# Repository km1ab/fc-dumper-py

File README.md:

# FC dumper py

- Dumper for fc by Python.
- This dumper is a HAT for Raspberry Pi and we also publish the source code to make it work in this repository.

## Environment
- Raspberry pi 3 b+, or later
- Raspberry pi zero, or later

```
Unsupported on Raspberry pi 5. "RPi.GPIO" is no longer available from Raspberry pi 5. 
We are currently looking into alternatives.
```

## How to use
At Raspberry pi, or remote connecting (ex ssh,...)
```
pip install RPi.GPIO
python3 fc_dumper.py -o filename
```

```
$ python3 fc_dumpter.py --help
usage: fc_dumpter.py [-h] [-o OUTPUT_FILE] [-p {8K,16K,32K}] [-c {1K,8K,16K,32K}] [-a {mapper0,mapper1,mapper3,mapper66,mapper23}] [-m {dumper,led_test}] [-d [DEBUG]] [-i [INFO]] [-s SIZE]
                     [-D [LED_DUTY ...]] [-F [LED_FREQ ...]] [-N [LED_NUMBER ...]] [-T LED_TIME]

options:
  -h, --help            show this help message and exit
  -o OUTPUT_FILE, --output_file OUTPUT_FILE
                        output file name; (default: output.nes)
  -p {8K,16K,32K}, --prg_rom_size {8K,16K,32K}
                        program rom size select; (default: 16K)
  -c {1K,8K,16K,32K}, --chr_rom_size {1K,8K,16K,32K}
                        charactor rom size select; (default: 8K)
  -a {mapper0,mapper1,mapper3,mapper66,mapper23}, --mapper {mapper0,mapper1,mapper3,mapper66,mapper23}
                        mapper select; In mapper 23, specify the size of the bank in options '-p' and '-c'. (default: mapper0)
  -m {dumper,led_test}, --mode {dumper,led_test}
                        mode (default: dumper)
  -d [DEBUG], --debug [DEBUG]
                        debug log (default: False)
  -i [INFO], --info [INFO]
                        game infomation (default: False)
  -s SIZE, --size SIZE  read size (default: 256)
  -D [LED_DUTY ...], --led_duty [LED_DUTY ...]
                        LED testing only (default: [1])
  -F [LED_FREQ ...], --led_freq [LED_FREQ ...]
                        LED testing only (default: [20])
  -N [LED_NUMBER ...], --led_number [LED_NUMBER ...]
                        LED testing only (default: [0])
  -T LED_TIME, --led_time LED_TIME
                        LED testing only (default: 5)
```

## Hardware
- PCB-top

- PCB-bottom

## Parts list
必須

| 名称                             | 数量 | 入手先      | 備考                                                                      |
|--------------------------------|----|----------|-------------------------------------------------------------------------|
| PCB-top (rev1.0)               | 1  | 頒布予定     | 本ページのHardwareを参照                                                        |
| PCB-bottom (rev1.0)            | 1  | 頒布予定     | 本ページのHardwareを参照                                                        |
| ラズパイ 3 b+                      | 1  | メルカリ？など  | ラズパイ5が発売されました。少々高いですが、容量の少ない方が比較的入手しやすいようです。2024/03現在。                    |
| CR22A-60D-2.54DS(70)           | 1  | ⇒⇒⇒      | googleにて、CR22A-60D-2.54DS(70)で検索すると、ある程度ヒットします。                         |
| 抵抗内蔵５ｍｍＬＥＤ（※）                  | 1  | 秋月電子     | https://akizukidenshi.com/catalog/g/gI-12517/                           |
| 小型スライドスイッチ　１回路２接点              | 1  | 秋月電子     | https://akizukidenshi.com/catalog/g/gP-12723/                           |
| 8ビット双方向ロジックレベル変換モジュール（FXMA108） | 1  | 秋月電子     | https://akizukidenshi.com/catalog/g/g104522/                            |
| 74HC244                        | 1  | マルツオンライン | https://www.marutsu.co.jp/GoodsDetail.jsp?salesGoodsCode=37576&shopNo=3 |
| 74HC4040                       | 2  | マルツオンライン | https://www.marutsu.co.jp/pc/i/18963/                                   |
| Raspberry Pi専用スペーサー（MPS-M2611） | 1  | サンハヤト    | https://shop.sunhayato.co.jp/products/mps-m2611                         |
| 六角オネジ・メネジ　ＭＢ２６－１１              | 4  | 秋月電子     | https://akizukidenshi.com/catalog/g/gP-11546/                           |
| ピンソケット (メス) 2×20 (40P)         | 1  | 秋月電子     | https://akizukidenshi.com/catalog/g/g100085/                            |
| ピンソケット(メス) 1×12(12P)           | 1  | 秋月電子     | https://akizukidenshi.com/catalog/g/g110101/                            |
| ピンソケット(メス) 1×10(10P)           | 1  | 秋月電子     | https://akizukidenshi.com/catalog/g/g103786/                            |
| ピンヘッダ 1×4 (4P)　10個入り（※）        | 1  | 秋月電子     | https://akizukidenshi.com/catalog/g/g103950/                            |
| ピンヘッダ 1×40 (40P)               | 1  | 秋月電子     | https://akizukidenshi.com/catalog/g/g100167/                            |
| ICソケット (16P)　10個入り（※）          | 1  | 秋月電子     | https://akizukidenshi.com/catalog/g/g100007/                            |
| ICソケット (20P)　10個入り（※）          | 1  | 秋月電子     | https://akizukidenshi.com/catalog/g/g100009/                            |

※LEDは、いかにも電源ONでスライドスイッチ真横のLED(D2)が光りそうですが、実際D3の方が光ります。<br>
　また、必ずしも内臓抵抗のものである必要がありません。<br>
　5mm LEDと抵抗の組み合わせでも良いです。<br>
　回路図をご覧頂くとわかるかと思います。<br>
※ピンヘッダ 1×4 (4P)は、1個しか使いません。バラで購入できるならそれで問題ありません。<br>
※ICソケットはそれぞれ2個使います。バラで購入できるならそれで問題ありません。<br>
　ただ、ICソケットは有りでも無しでも好きな方で。<br>

#### オプション
- 抵抗内蔵５ｍｍＬＥＤ x2
- トランジスタ　２ＳＣ１８１５ x2
- ※抵抗内蔵LEDを使わない場合は、抵抗x3（抵抗値はLEDのスペックによる）
- Bottom ケース：3Dプリンタで作りました。3B+用に適当に作っています　(データ：stl/raspi_case_4_2.stl)
- ピンヘッダ 2×20 (40P) ※2x4(8P)分しか使いません。デバッグ用なので無くても問題ありせん。
### 完成図
- ラズパイと接続するとこのような見た目になります。
- ２段のスタック構造になっています。
- ※Raspberry Pi専用スペーサーのナットは使いませんでした。

### 分割した様子
#### face and bottom
- face

- bottom

### 留意事項
#### FXMA108の取り付けについて
- FXMA108のキットは、付属のピンヘッダをそのまま取り付けると、隣のHC244より背が高くなります。<br>それに伴い、PCB-TOPをスタックする時に干渉してしまいますので、以下に取付方法を記載致します。
- 方法１
  - ピンヘッダの足を適当な長さに切りそろえて下さい。
  - また、付属のピンヘッダの足は太いので、ICソケットに若干強引に差し込みます（問題なくささりますが）。
  - なので、気になる方は細ピンヘッダを使うと良いかもしれません。
- もう１つの方法
  - ICソケットも、ピンヘッダも使わずに直に取り付けてしまう方法です。
  - FXMA108のキットに以下のような説明がありました。簡単な方をお試しください。
```
スルーホール部分をルータ加工することで、ユニバーサル基板等に直接ハンダ付け可能となっています。（※）
```
※8ビット双方向ロジックレベル変換モジュールのマニュアルより引用。

### PCB design

#### top PCB

#### bottom PCB

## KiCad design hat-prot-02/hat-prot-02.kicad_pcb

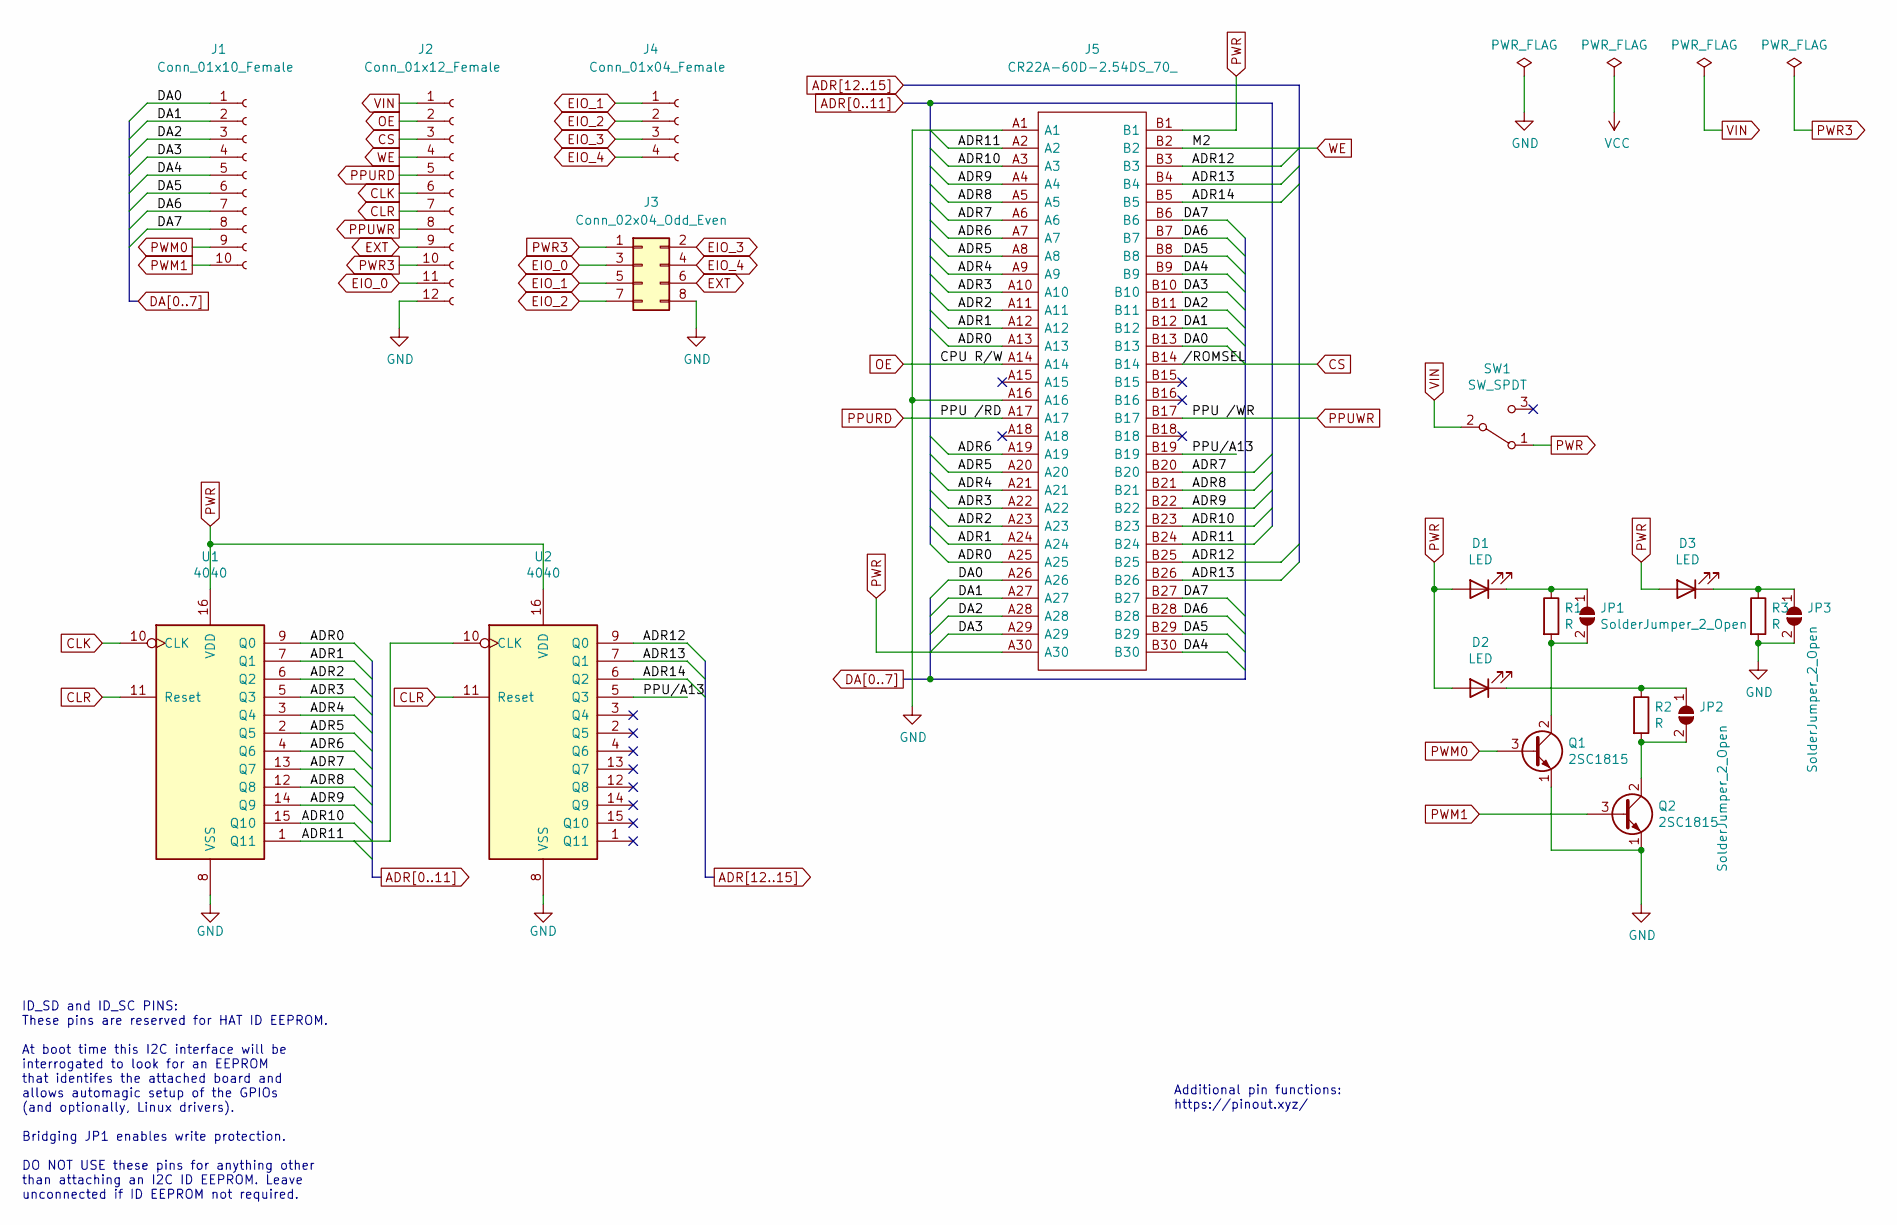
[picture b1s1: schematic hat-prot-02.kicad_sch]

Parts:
D1, D2, D3: LED; LED_D3.0mm
J1: Conn_01x10_Female; PinSocket_1x10_P2.54mm_Vertical
J2: Conn_01x12_Female; PinSocket_1x12_P2.54mm_Vertical
J3: Conn_02x04_Odd_Even; PinHeader_2x04_P2.54mm_Vertical
J4: Conn_01x04_Female; PinSocket_1x04_P2.54mm_Vertical
J5: CR22A-60D-2.54DS_70_; CR22A60D254DS70; Manufacturer_Part_Number CR22A-60D-2.54DS(70)
JP1, JP2, JP3: SolderJumper_2_Open; SolderJumper-2_P1.3mm_Open_RoundedPad1.0x1.5mm
Q1, Q2: 2SC1815; TO-92_Inline
R1, R2, R3: R; R_Axial_DIN0204_L3.6mm_D1.6mm_P5.08mm_Horizontal
SW1: SW_SPDT; PinHeader_1x03_P2.54mm_Vertical
U1, U2: 4040; DIP-16_W7.62mm

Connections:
/PPU/A13: J5.B19, U2.5 (Q3)
ADR0: J5.A13, J5.A25, U1.9 (Q0)
ADR1: J5.A12, J5.A24, U1.7 (Q1)
ADR2: J5.A11, J5.A23, U1.6 (Q2)
ADR3: J5.A10, J5.A22, U1.5 (Q3)
ADR4: J5.A9, J5.A21, U1.3 (Q4)
ADR5: J5.A8, J5.A20, U1.2 (Q5)
ADR6: J5.A7, J5.A19, U1.4 (Q6)
ADR7: J5.A6, J5.B20, U1.13 (Q7)
ADR8: J5.A5, J5.B21, U1.12 (Q8)
ADR9: J5.A4, J5.B22, U1.14 (Q9)
ADR10: J5.A3, J5.B23, U1.15 (Q10)
ADR11: J5.A2, J5.B24, U1.1 (Q11), U2.10 (CLK)
ADR12: J5.B3, J5.B25, U2.9 (Q0)
ADR13: J5.B4, J5.B26, U2.7 (Q1)
ADR14: J5.B5, U2.6 (Q2)
CLK: J2.6, U1.10 (CLK)
CLR: J2.7, U1.11 (Reset), U2.11 (Reset)
CS: J2.3, J5.B14
DA0: J1.1, J5.A26, J5.B13
DA1: J1.2, J5.A27, J5.B12
DA2: J1.3, J5.A28, J5.B11
DA3: J1.4, J5.A29, J5.B10
DA4: J1.5, J5.B9, J5.B30
DA5: J1.6, J5.B8, J5.B29
DA6: J1.7, J5.B7, J5.B28
DA7: J1.8, J5.B6, J5.B27
EIO_0: J2.11, J3.3
EIO_1: J3.5, J4.1
EIO_2: J3.7, J4.2
EIO_3: J3.2, J4.3
EIO_4: J3.4, J4.4
EXT: J2.9, J3.6
unnamed: D1.1 (K), JP1.1 (A), R1.1
unnamed: D2.1 (K), JP2.1 (A), R2.1
unnamed: D3.1 (K), JP3.1 (A), R3.1
unnamed: JP1.2 (B), Q1.2 (C), R1.2
unnamed: JP2.2 (B), Q2.2 (C), R2.2
OE: J2.2, J5.A14
PPURD: J2.5, J5.A17
PPUWR: J2.8, J5.B17
PWM0: J1.9, Q1.3 (B)
PWM1: J1.10, Q2.3 (B)
PWR: D1.2 (A), D2.2 (A), D3.2 (A), J5.A30, J5.B1, SW1.1 (A), U1.16 (VDD), U2.16 (VDD)
WE: J2.4, J5.B2

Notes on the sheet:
Additional pin functions: https://pinout.xyz/
ID_SD and ID_SC PINS: These pins are reserved for HAT ID EEPROM. At boot time this I2C interface will be interrogated to look for an EEPROM that identifes the attached board and allows automagic setup of the GPIOs (and optionally, Linux drivers). Bridging JP1 enables write protection. DO NOT USE th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

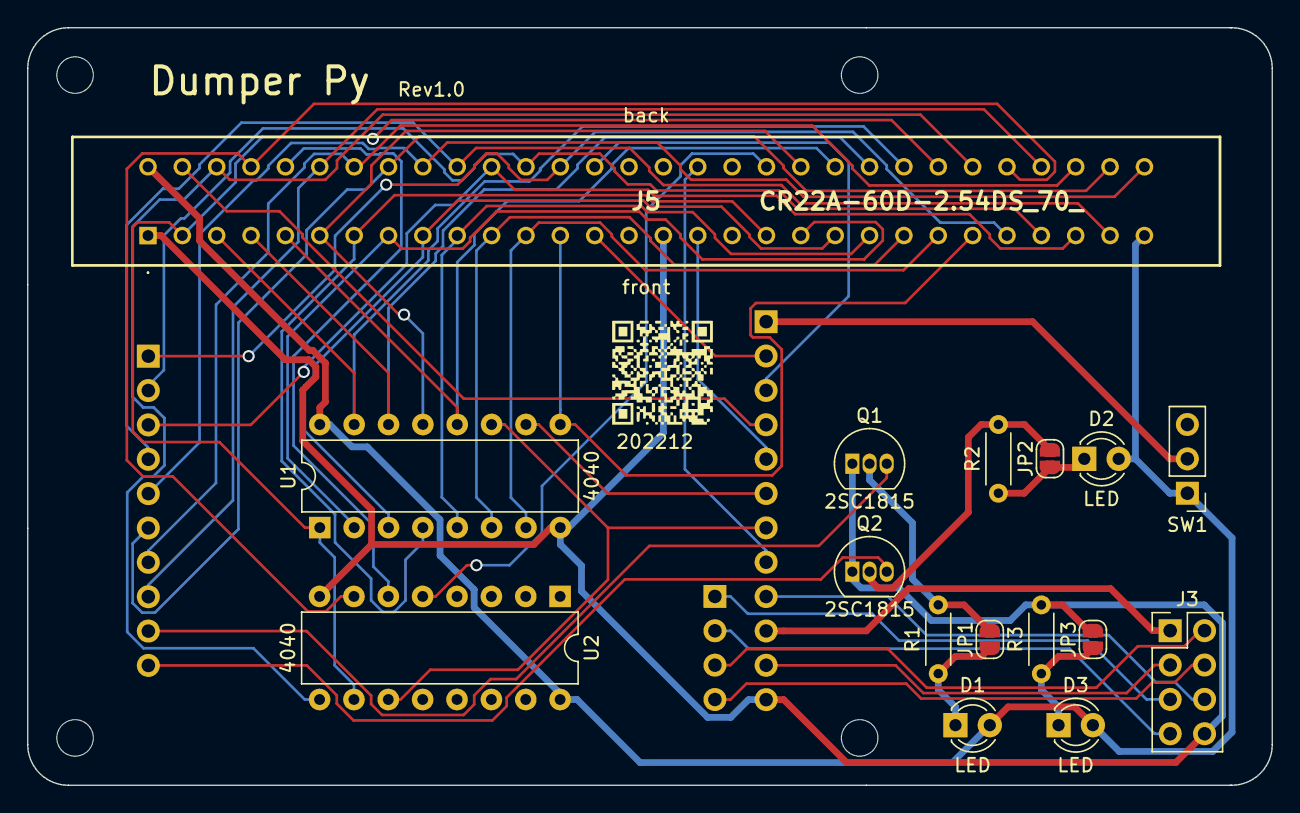
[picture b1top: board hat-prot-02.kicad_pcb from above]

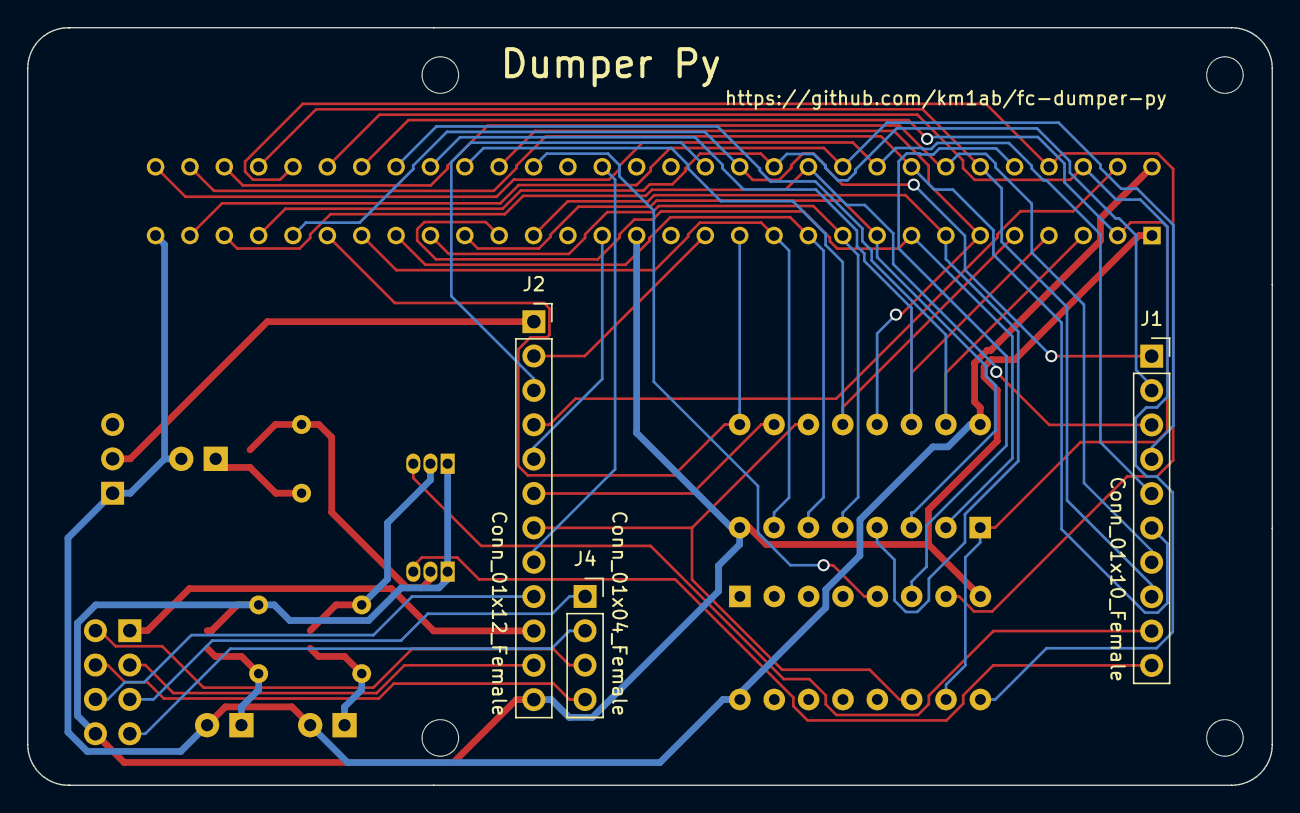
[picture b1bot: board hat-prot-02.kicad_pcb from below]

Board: 2 copper layers, 92.0 x 56.0 mm, 23 parts (3 on the bottom side), 48 nets.

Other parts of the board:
MH1, MH2, MH3, MH4: MountingHole_2.7mm_M2.5

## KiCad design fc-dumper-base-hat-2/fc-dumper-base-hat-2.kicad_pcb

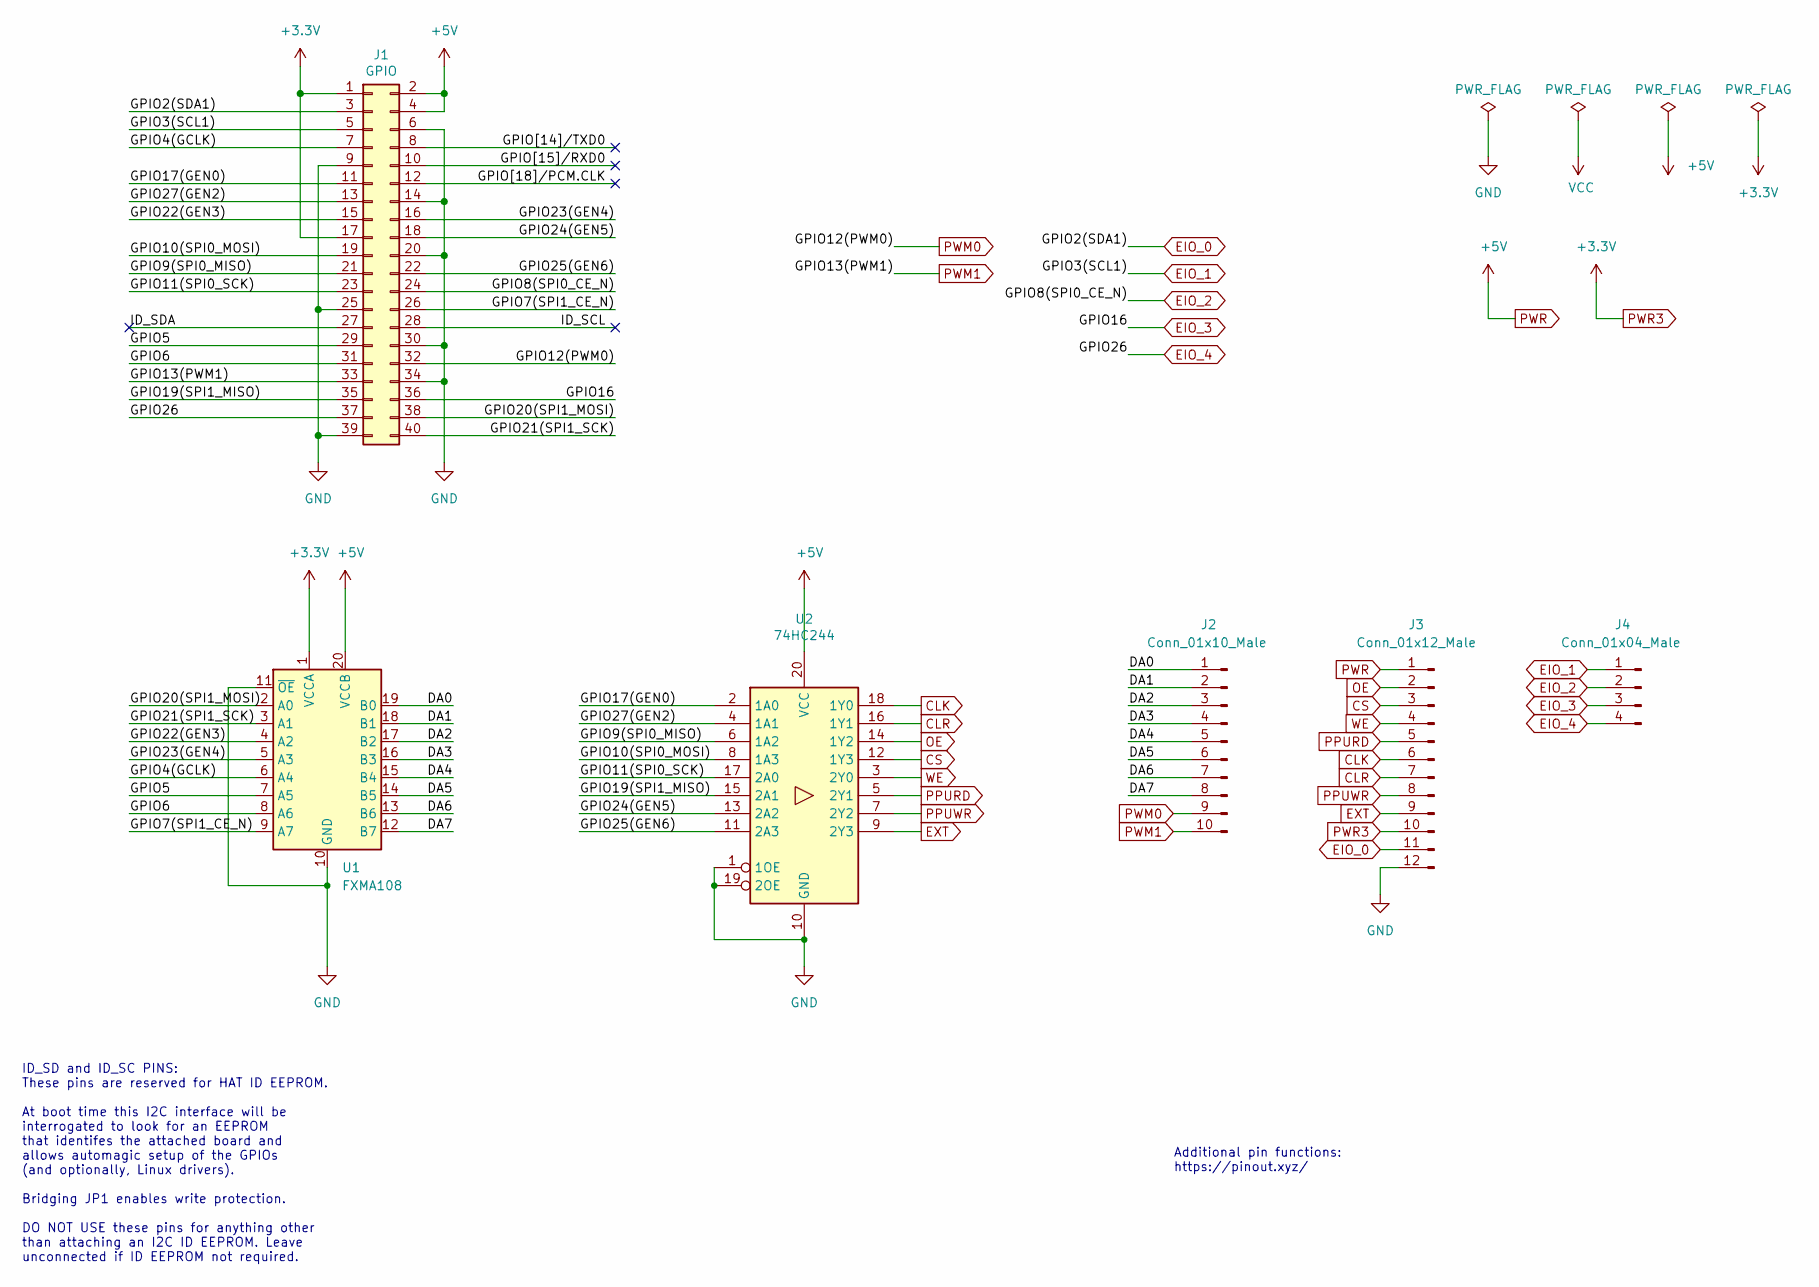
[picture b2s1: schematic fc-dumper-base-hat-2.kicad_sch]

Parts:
J1: GPIO; PinSocket_2x20_P2.54mm_Vertical
J2: Conn_01x10_Male; PinHeader_1x10_P2.54mm_Vertical
J3: Conn_01x12_Male; PinHeader_1x12_P2.54mm_Vertical
J4: Conn_01x04_Male; PinHeader_1x04_P2.54mm_Vertical
U1: FXMA108; DIP-20_W7.62mm
U2: 74HC244; DIP-20_W7.62mm

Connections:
/DA0: J2.1, U1.19 (B0)
/DA1: J2.2, U1.18 (B1)
/DA2: J2.3, U1.17 (B2)
/DA3: J2.4, U1.16 (B3)
/DA4: J2.5, U1.15 (B4)
/DA5: J2.6, U1.14 (B5)
/DA6: J2.7, U1.13 (B6)
/DA7: J2.8, U1.12 (B7)
/GPIO4(GCLK): J1.7, U1.6 (A4)
/GPIO5: J1.29, U1.7 (A5)
/GPIO6: J1.31, U1.8 (A6)
/GPIO7(SPI1_CE_N): J1.26, U1.9 (A7)
/GPIO9(SPI0_MISO): J1.21, U2.6 (1A2)
/GPIO10(SPI0_MOSI): J1.19, U2.8 (1A3)
/GPIO11(SPI0_SCK): J1.23, U2.17 (2A0)
/GPIO17(GEN0): J1.11, U2.2 (1A0)
/GPIO19(SPI1_MISO): J1.35, U2.15 (2A1)
/GPIO20(SPI1_MOSI): J1.38, U1.2 (A0)
/GPIO21(SPI1_SCK): J1.40, U1.3 (A1)
/GPIO22(GEN3): J1.15, U1.4 (A2)
/GPIO23(GEN4): J1.16, U1.5 (A3)
/GPIO24(GEN5): J1.18, U2.13 (2A2)
/GPIO25(GEN6): J1.22, U2.11 (2A3)
/GPIO27(GEN2): J1.13, U2.4 (1A1)
/GPIO[14]/TXD0: J1.8
/GPIO[15]/RXD0: J1.10
/GPIO[18]/PCM.CLK: J1.12
/ID_SCL: J1.28
/ID_SDA: J1.27
CLK: J3.6, U2.18 (1Y0)
CLR: J3.7, U2.16 (1Y1)
CS: J3.3, U2.12 (1Y3)
EIO_0: J1.3, J3.11
EIO_1: J1.5, J4.1
EIO_2: J1.24, J4.2
EIO_3: J1.36, J4.3
EIO_4: J1.37, J4.4
EXT: J3.9, U2.9 (2Y3)
GND: J1.6, J1.9, J1.14, J1.20, J1.25, J1.30, J1.34, J1.39, J3.12, U1.10 (GND), U1.11 (~OE), U2.1 (1OE), U2.10 (GND), U2.19 (2OE)
OE: J3.2, U2.14 (1Y2)
PPURD: J3.5, U2.5 (2Y1)
PPUWR: J3.8, U2.7 (2Y2)
PWM0: J1.32, J2.9
PWM1: J1.33, J2.10
PWR: J1.2, J1.4, J3.1, U1.20 (VCCB), U2.20 (VCC)
PWR3: J1.1, J1.17, J3.10, U1.1 (VCCA)
WE: J3.4, U2.3 (2Y0)

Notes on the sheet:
Additional pin functions: https://pinout.xyz/
ID_SD and ID_SC PINS: These pins are reserved for HAT ID EEPROM. At boot time this I2C interface will be interrogated to look for an EEPROM that identifes the attached board and allows automagic setup of the GPIOs (and optionally, Linux drivers). Bridging JP1 enables write protection. DO NOT USE th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

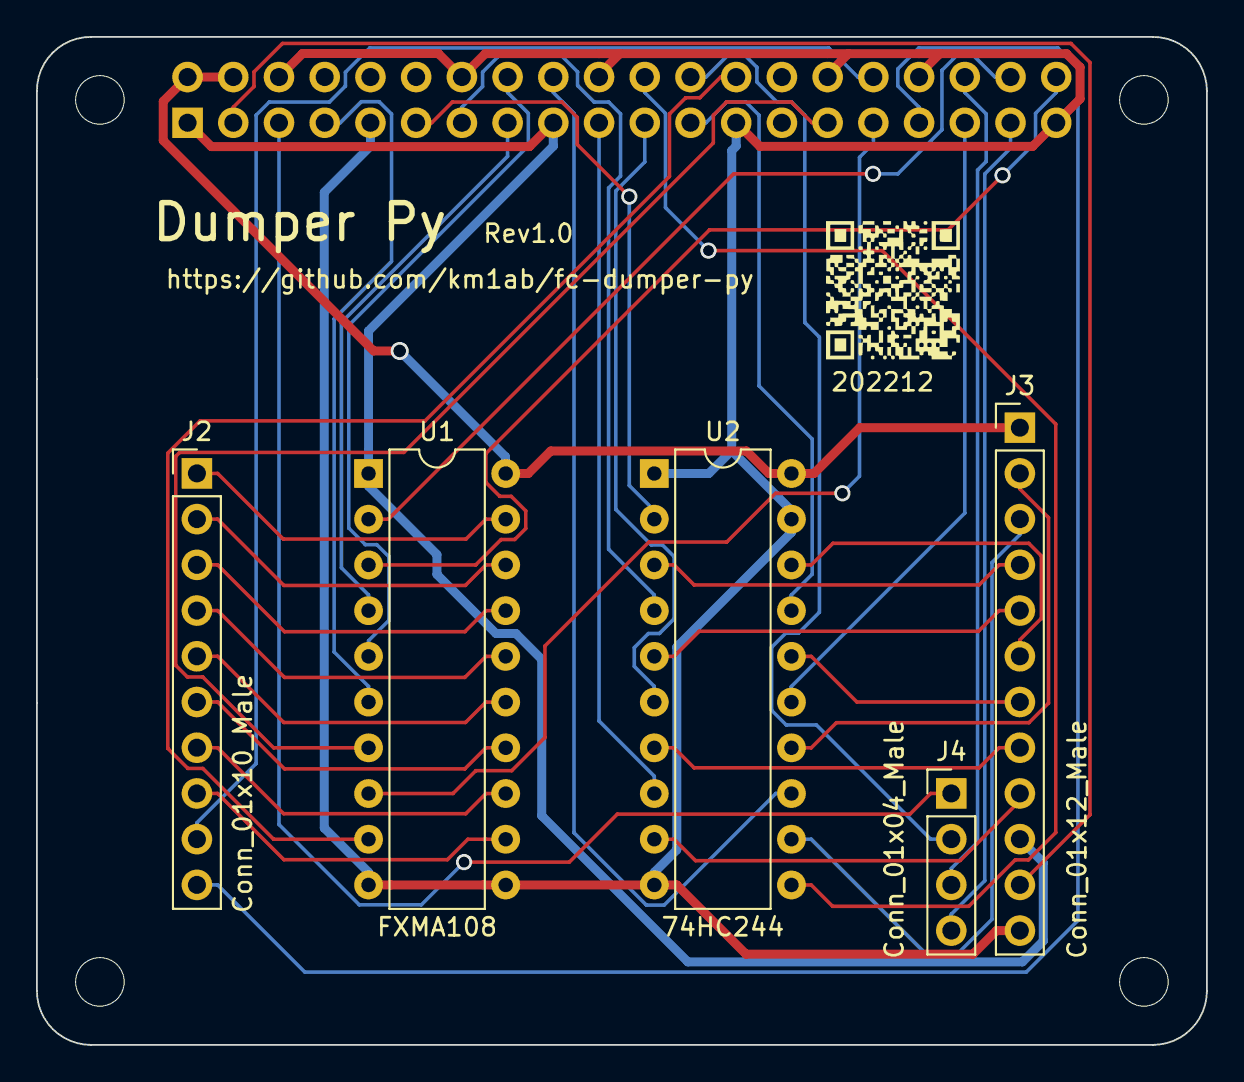
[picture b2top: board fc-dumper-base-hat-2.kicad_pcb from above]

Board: 2 copper layers, 65.0 x 56.0 mm, 10 parts (1 on the bottom side), 42 nets.

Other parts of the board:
MH1, MH2, MH3, MH4: MountingHole_2.7mm_M2.5

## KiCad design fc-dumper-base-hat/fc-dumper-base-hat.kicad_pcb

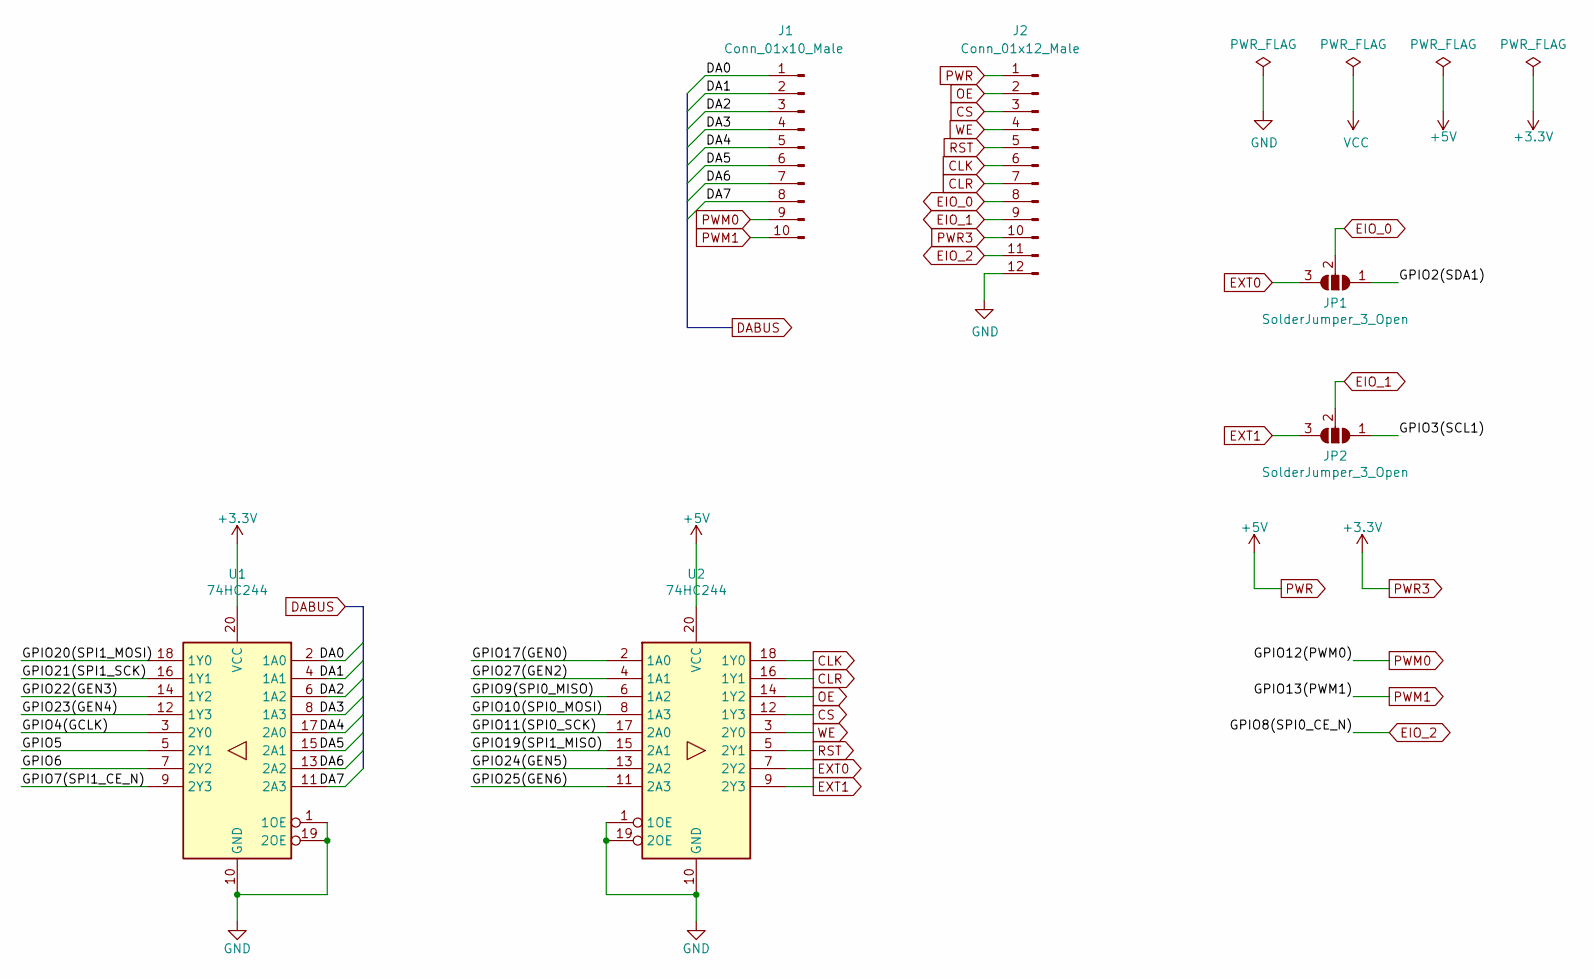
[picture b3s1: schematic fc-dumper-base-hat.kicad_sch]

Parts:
J1: Conn_01x10_Male; PinHeader_1x10_P2.54mm_Vertical
J2: Conn_01x12_Male; PinHeader_1x12_P2.54mm_Vertical
JP1, JP2: SolderJumper_3_Open; SolderJumper-3_P1.3mm_Open_RoundedPad1.0x1.5mm_NumberLabels
U1, U2: 74HC244; DIP-20_W7.62mm

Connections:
/DA0: J1.1, U1.2 (1A0)
/DA1: J1.2, U1.4 (1A1)
/DA2: J1.3, U1.6 (1A2)
/DA3: J1.4, U1.8 (1A3)
/DA4: J1.5, U1.17 (2A0)
/DA5: J1.6, U1.15 (2A1)
/DA6: J1.7, U1.13 (2A2)
/DA7: J1.8, U1.11 (2A3)
/GPIO2(SDA1): JP1.1 (A); also elsewhere on the board
/GPIO3(SCL1): JP2.1 (A); also elsewhere on the board
/GPIO4(GCLK): U1.3 (2Y0); also elsewhere on the board
/GPIO5: U1.5 (2Y1); also elsewhere on the board
/GPIO6: U1.7 (2Y2); also elsewhere on the board
/GPIO7(SPI1_CE_N): U1.9 (2Y3); also elsewhere on the board
/GPIO9(SPI0_MISO): U2.6 (1A2); also elsewhere on the board
/GPIO10(SPI0_MOSI): U2.8 (1A3); also elsewhere on the board
/GPIO11(SPI0_SCK): U2.17 (2A0); also elsewhere on the board
/GPIO17(GEN0): U2.2 (1A0); also elsewhere on the board
/GPIO19(SPI1_MISO): U2.15 (2A1); also elsewhere on the board
/GPIO20(SPI1_MOSI): U1.18 (1Y0); also elsewhere on the board
/GPIO21(SPI1_SCK): U1.16 (1Y1); also elsewhere on the board
/GPIO22(GEN3): U1.14 (1Y2); also elsewhere on the board
/GPIO23(GEN4): U1.12 (1Y3); also elsewhere on the board
/GPIO24(GEN5): U2.13 (2A2); also elsewhere on the board
/GPIO25(GEN6): U2.11 (2A3); also elsewhere on the board
/GPIO27(GEN2): U2.4 (1A1); also elsewhere on the board
CLK: J2.6, U2.18 (1Y0)
CLR: J2.7, U2.16 (1Y1)
CS: J2.3, U2.12 (1Y3)
EIO_0: J2.8, JP1.2 (C)
EIO_1: J2.9, JP2.2 (C)
EIO_2: J2.11; also elsewhere on the board
EXT0: JP1.3 (B), U2.7 (2Y2)
EXT1: JP2.3 (B), U2.9 (2Y3)
GND: J2.12, U1.1 (1OE), U1.10 (GND), U1.19 (2OE), U2.1 (1OE), U2.10 (GND), U2.19 (2OE); also elsewhere on the board
OE: J2.2, U2.14 (1Y2)
PWM0: J1.9; also elsewhere on the board
PWM1: J1.10; also elsewhere on the board
PWR: J2.1, U2.20 (VCC); also elsewhere on the board
PWR3: J2.10, U1.20 (VCC); also elsewhere on the board
RST: J2.5, U2.5 (2Y1)
WE: J2.4, U2.3 (2Y0)

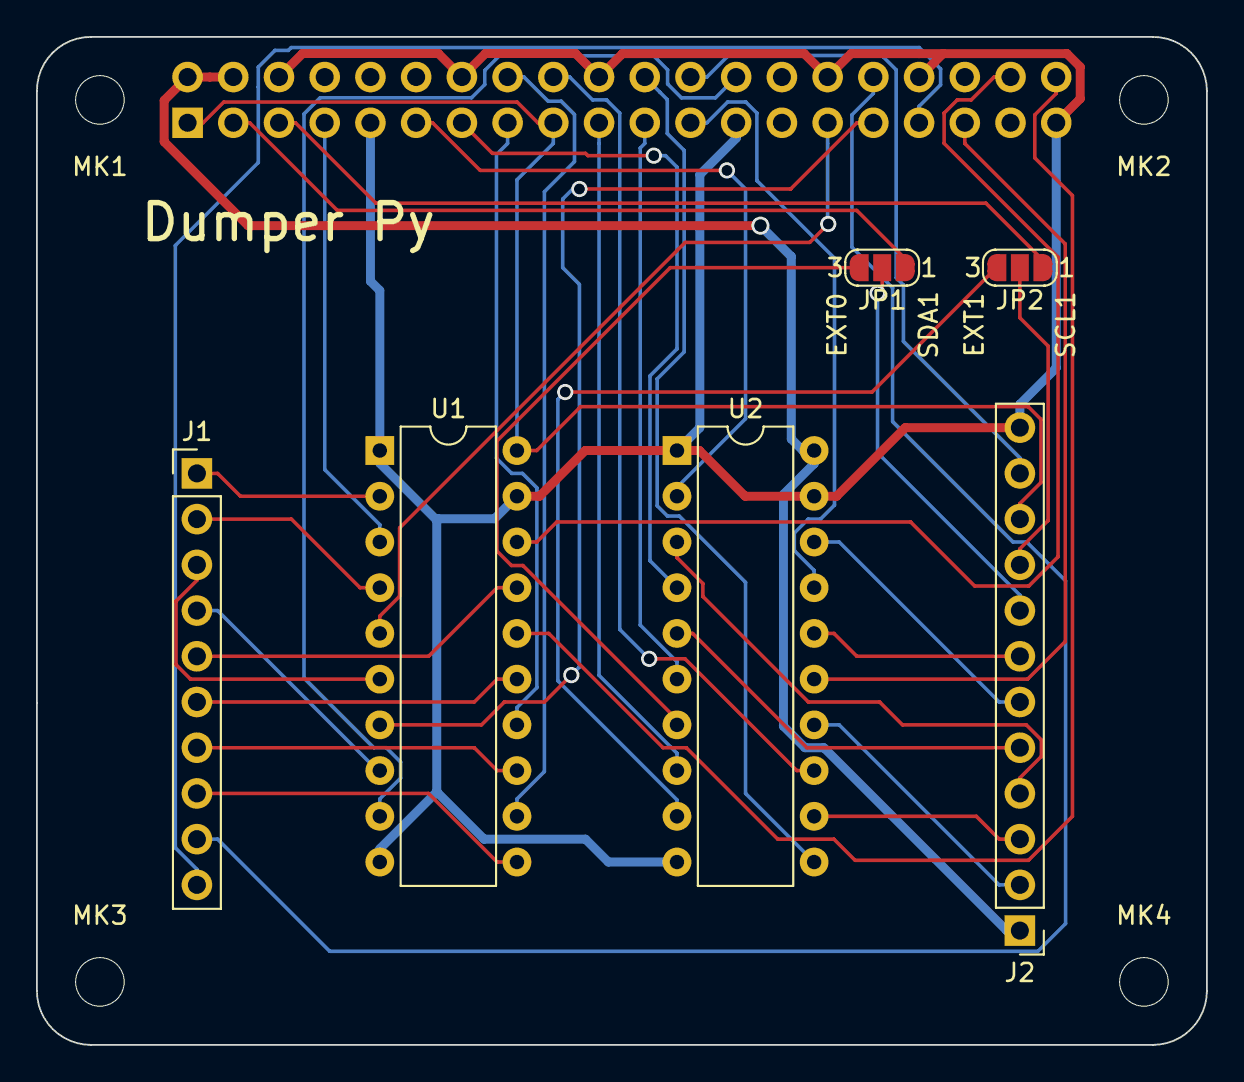
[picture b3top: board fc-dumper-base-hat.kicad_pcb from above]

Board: 2 copper layers, 65.0 x 56.0 mm, 11 parts (1 on the bottom side), 42 nets.

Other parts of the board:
MK1, MK2, MK3, MK4: M2.5; MountingHole_2.7mm_M2.5
P1: Conn_02x20_Odd_Even; PinSocket_2x20_P2.54mm_Vertical

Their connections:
/GPIO2(SDA1): P1.3; also elsewhere on the board
/GPIO3(SCL1): P1.5; also elsewhere on the board
/GPIO4(GCLK): P1.7; also elsewhere on the board
/GPIO5: P1.29; also elsewhere on the board
/GPIO6: P1.31; also elsewhere on the board
/GPIO7(SPI1_CE_N): P1.26; also elsewhere on the board
/GPIO9(SPI0_MISO): P1.21; also elsewhere on the board
/GPIO10(SPI0_MOSI): P1.19; also elsewhere on the board
/GPIO11(SPI0_SCK): P1.23; also elsewhere on the board
/GPIO17(GEN0): P1.11; also elsewhere on the board
/GPIO19(SPI1_MISO): P1.35; also elsewhere on the board
/GPIO20(SPI1_MOSI): P1.38; also elsewhere on the board
/GPIO21(SPI1_SCK): P1.40; also elsewhere on the board
/GPIO22(GEN3): P1.15; also elsewhere on the board
/GPIO23(GEN4): P1.16; also elsewhere on the board
/GPIO24(GEN5): P1.18; also elsewhere on the board
/GPIO25(GEN6): P1.22; also elsewhere on the board
/GPIO27(GEN2): P1.13; also elsewhere on the board
EIO_2: P1.24; also elsewhere on the board
GND: P1.6, P1.9, P1.14, P1.20, P1.25, P1.30, P1.34, P1.39; also elsewhere on the board
PWM0: P1.32; also elsewhere on the board
PWM1: P1.33; also elsewhere on the board
PWR: P1.2, P1.4; also elsewhere on the board
PWR3: P1.1, P1.17; also elsewhere on the board

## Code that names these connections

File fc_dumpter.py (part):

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port_tbl_addr_ctrl = [17, 27]

port_tbl_data_ctrl = [20, 21, 22, 23, 4, 5, 6, 7]
# CPU R/W	# /ROMSEL	# M2	# PPU /RD   # PPU /WR  # EXT PIN
port_tbl_port_ctrl = [9, 10, 11, 19, 24, 25]

# PWM0 # PWM1
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        #   PRG ROMの/OEと/ROMSELが接続。/OEなので0でenable
        # M2=1
        #   マッパー0の回路図を見るとM2(O2)がない。実質Don't care
        # PPUWR=1
        #   マッパー0の回路図を見ると/WEがない。1で無効にしておく。実質Don't care
        # PPURD=1
        #   CHR ROMの/OEと/RDが接続。1で無効にしておく。
        #   また、CHR ROMのPA13と/CSが接続
        set_cpu_rw()
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        #   PRG ROMの/OEと/ROMSELが接続。/OEなので1でdisable
        # M2=1
        #   マッパー0の回路図を見るとM2(O2)がない。実質Don't care
        # PPUWR=1
        #   マッパー0の回路図を見ると/WEがない。1で無効にしておく。実質Don't care
        # PPURD=1
        #   CHR ROMの/OEと/RDが接続。1で無効にしておく。
        #   また、CHR ROMのPA13と/CSが接続。PA13=0にすることでCHR ROM選択。
        unset_cpu_rw()
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
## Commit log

2022-12-10 add design data
2022-12-10 update design, and document
2022-12-11 modify design delete copy add QR code
2022-12-11 add QR code to botom-PCB
2022-12-13 update design
2022-12-16 add version silk
2022-12-17 add tools gerber data
2022-12-17 add gerber data
2022-12-17 complete gerber
2022-12-17 add README.md, and images, gerber zip.
2022-12-17 update convert script. apply windows platform.
2022-12-18 update tool
2022-12-25 add option, led test, add select option (size and mapper)
2022-12-27 add RomDumper class add mapper3, meijin test OK
2022-12-27 modify code-format snakecase
2022-12-27 add hint, test OK star.
2022-12-28 apply bank-key for mapper3 add debug mode
2022-12-29 apply header for mapper0 and mapper3 apply mapper66, test dora ok
2023-01-09 add mapper3, test fxa ok!!
2023-07-30 add mapper23 info add debug info mapper23 OK (VRC2b)
2023-07-30 add comment
2024-02-26 add design data update design, and document
2024-02-26 add QR code to botom-PCB update design add version silk
2024-02-26 add tools, gerber data complete gerber
2024-02-26 add README.md, and images
2024-02-26 add Dumper script
2024-03-17 update doc and PCB images
2024-03-17 add attention
2024-03-17 add 3d print data (stl)
2024-03-17 add schematic
2024-03-17 Organized description of FXMA108, fix else.
2024-07-17 A note has been added to the support information.
